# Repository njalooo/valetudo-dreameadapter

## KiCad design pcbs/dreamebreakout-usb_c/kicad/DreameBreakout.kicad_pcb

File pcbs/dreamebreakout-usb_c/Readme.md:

# Dreame Breakout USB-C Version

This breakout PCB takes the 2.0mm pitch 2x8P dreame debug header and breaks that out into a more usable form.

Specifically it provides
- All pins on two 2.54mm pitch headers for use with regular jumper wires etc
- A USB-C socket for flashing stuff via FEL, Livesuit etc.
- A USB A socket for USB OTG use
- A button to pull BSel to GND to enter FEL
- A jumper to enable USB OTG

**Important:** <br/>
The PCB needs to be manufactured with 1.2mm thickness or else the robot-facing connector won't fit

## Bill of Materials

All the parts required should be available on Aliexpress or similar.

- 1x 2.00mm pitch 2x8P male header
- 2x 2.54mm pitch 1x8P female header
- 1x 6x6mm tactile button
- 1x USB-C port (Here GCT USB4145-03-0230-C)
- 1x USB A port
- 2x 5.1kΩ ±20% Resistor. This is neccessary so that the USB-C host device will provide power via VBus.

Optional (can also be done via a regular jumper wire using the larger headers):
- 2x 2.00mm pitch 1x2P male header
- 2x 2.00mm pitch jumper

Keep in mind that there are many different types of USB connectors available on the market.
To make sure that you buy the right parts with the correct footprints, you can use the pictures from the soldering guide below as a reference.

## Assembly

## Soldering guide 

All images in this guide are also links pointing to a higher-res version of them. Make sure to take advantage of that. 

We'll start with an overview shot of all parts you will need.

As the first step, take the robot-facing header and solder it to the PCB.
Do **only a single outer pin first**, then check the alignment and re-align if needed.

Re-aligning with multiple pins soldered will be much harder so make sure to do it correctly.
But also don't worry too much about it as it does not have to be perfect as you can see in the example PCB:

Next up is the Micro USB port. This is probably the scariest part but actually it's not that hard as you can easily access the only five tiny pins.
Place the port on the PCB and use the USB A port to prop up the PCB to align the Micro USB port correctly.

Now, start by soldering the two outer large shield connection points to pin the port in place and then check the alignment. Re-align if needed.
After that, solder the five inner pins. Make sure to not bridge them. If you do have a solder bridge, you can get usually
get rid of it by dragging the soldering iron through the pins as the solder will prefer sticking to the iron instead of the pins.

The next part is the 2-position 2.00mm pitch header for the USB OTG ID jumper.
For that, continue using the USB A port to hold the PCB at the right height and make sure that the header is aligned properly.

Continue by soldering the button to the PCB. Make sure to orient it correctly.
For that, pay close attention to the curvature of its legs in the following picture:

Because of those legs, the button will be fixed in place so you won't be needing the USB A port for alignment anymore.

Next up are the 2.54mm pitch breakout headers. Place them on a flat surface and put the PCB on top like this:

Ensure that they're aligned correctly and then start by soldering just a single leg on the outside on each of them like you did in Step 1 to allow for alignment correction.

When you're happy with the alignment, solder the other end of the connector and then continue to fill in the rest of the pins.

To solder the final USB A connector, you will need something else to prop up the PCB. I've used scissors here.
I'm sure you'll find something that has the right height.

As with the Micro USB connector, start with the two large shield connections on the outside, once again, re-check the alignment and realign as needed.
Then, solder the four inner pins.

Congratulations! You have successfully built a dreame breakout PCB.

If this was helpful to you, there's the option of leaving a tip using [GitHub sponsors](https://github.com/sponsors/Hypfer/).

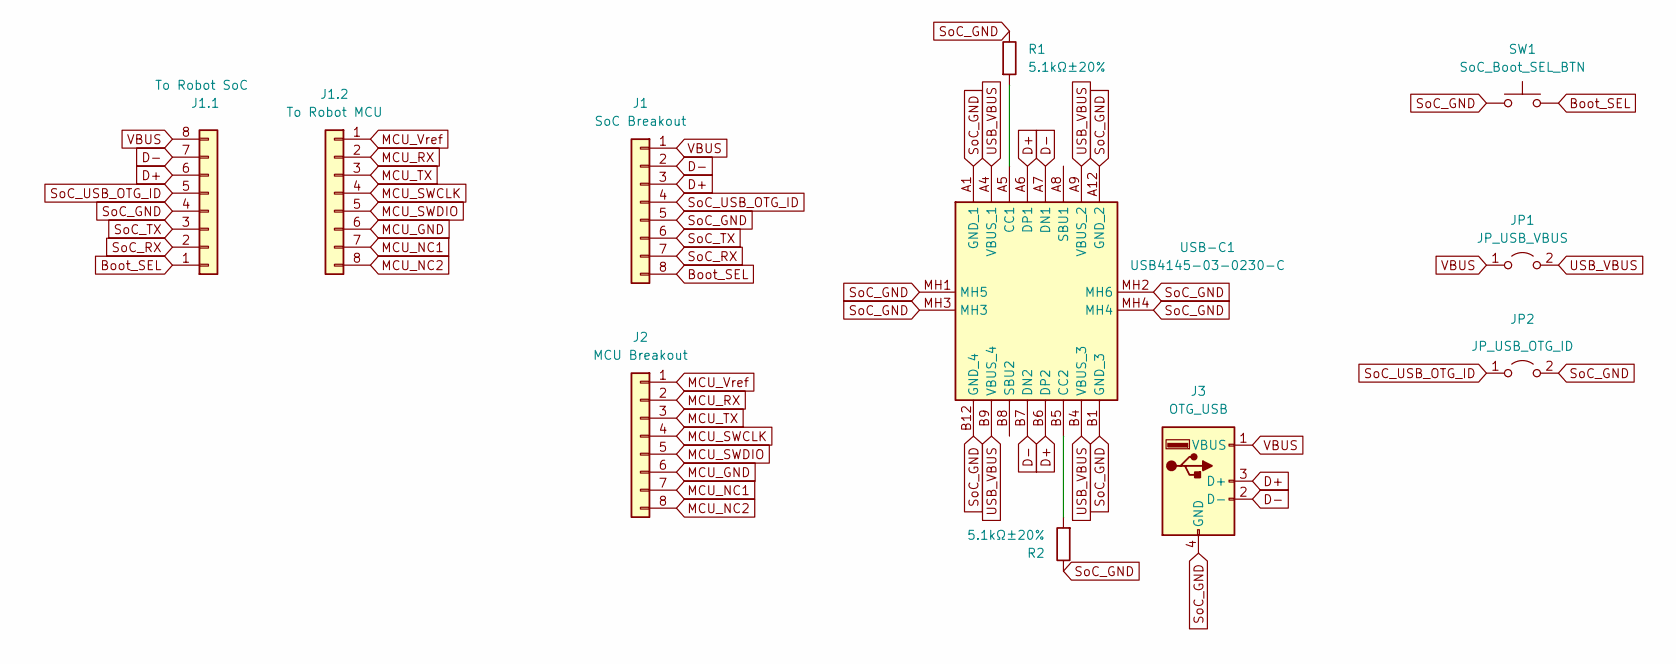
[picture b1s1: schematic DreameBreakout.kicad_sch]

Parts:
J1: SoC Breakout; PinSocket_1x08_P2.54mm_Vertical
J1.1: To Robot SoC; DGI_8_SMDPADS
J1.2: To Robot MCU; DGI_8_SMDPADS
J2: MCU Breakout; PinSocket_1x08_P2.54mm_Vertical
J3: OTG_USB; ONSHORE_USB-A1VSB6
JP1: JP_USB_VBUS; PinSocket_1x02_P2.00mm_Vertical
JP2: JP_USB_OTG_ID; PinSocket_1x02_P2.00mm_Vertical
R1, R2: 5.1kΩ±20%; R_Axial_DIN0204_L3.6mm_D1.6mm_P7.62mm_Horizontal
SW1: SoC_Boot_SEL_BTN; SW_PUSH_6mm
USB-C1: USB4145-03-0230-C; USB4145030230C; Mouser Part Number 640-USB4145-3-0230-C

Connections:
Boot_SEL: J1.8, J1.1.1, SW1.2
D+: J1.3, J1.1.6, J3.3 (D+), USB-C1.A6 (DP1), USB-C1.B6 (DP2)
D-: J1.2, J1.1.7, J3.2 (D-), USB-C1.A7 (DN1), USB-C1.B7 (DN2)
MCU_GND: J1.2.6, J2.6
MCU_NC1: J1.2.7, J2.7
MCU_NC2: J1.2.8, J2.8
MCU_RX: J1.2.2, J2.2
MCU_SWCLK: J1.2.4, J2.4
MCU_SWDIO: J1.2.5, J2.5
MCU_TX: J1.2.3, J2.3
MCU_Vref: J1.2.1, J2.1
unnamed: R1.1, USB-C1.A5 (CC1)
unnamed: R2.1, USB-C1.B5 (CC2)
SoC_GND: J1.5, J1.1.4, J3.4 (GND), JP2.2 (B), R1.2, R2.2, SW1.1, USB-C1.A1 (GND_1), USB-C1.A12 (GND_2), USB-C1.B1 (GND_3), USB-C1.B12 (GND_4), USB-C1.MH1 (MH5), USB-C1.MH2 (MH6), USB-C1.MH3, USB-C1.MH4
SoC_RX: J1.7, J1.1.2
SoC_TX: J1.6, J1.1.3
SoC_USB_OTG_ID: J1.4, J1.1.5, JP2.1 (A)
USB_VBUS: JP1.2 (B), USB-C1.A4 (VBUS_1), USB-C1.A9 (VBUS_2), USB-C1.B4 (VBUS_3), USB-C1.B9 (VBUS_4)
VBUS: J1.1, J1.1.8, J3.1 (VBUS), JP1.1 (A)

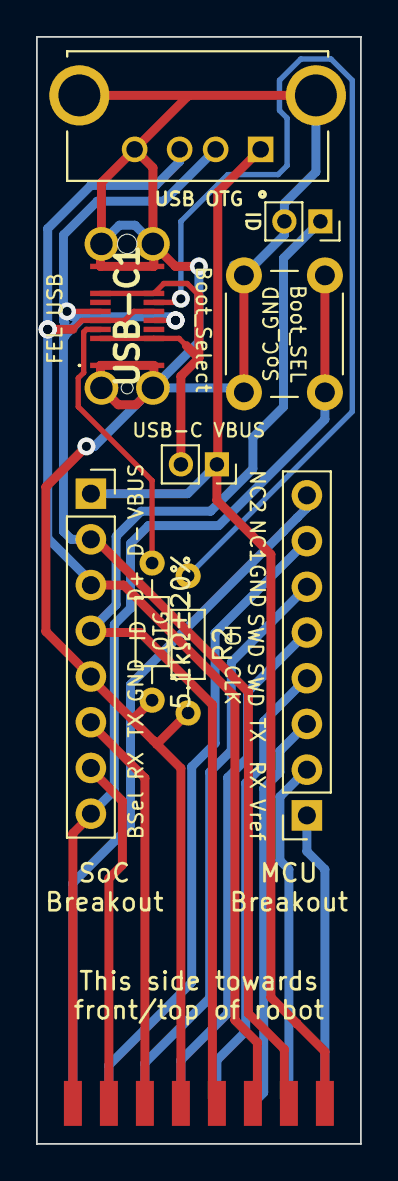
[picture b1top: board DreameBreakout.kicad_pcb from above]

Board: 2 copper layers, 18.0 x 61.5 mm, 11 parts (1 on the bottom side), 19 nets.

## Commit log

2024-08-05 Replaced micro-USB with USB-C port
2024-08-05 Added image for visualisation
2024-08-05 Copied images for Readme
2024-08-05 Replaced micro-USB with USB-C receptacle. Also added a second Resistor for symeptric pluggablility
